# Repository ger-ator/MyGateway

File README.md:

# MyGateway
RFM69 + ATSHA204A Shield for Arduino.

# Description
This is another shield to build a MySensors gateway with Arduino UNO form factor. 
It includes RFM69 radio module and ATSHA204A crypto signing chip.

# Configuration
There are two jumpers to configure CS and IRQ RFM69 pins.
JP1 is used to choose between pins 6 or 10 for the RFM69 CS line. This is necessary to use an ethernet module in the same SPI bus.
JP2 is used to choose between pins 2 or 3 for the RFM69 IRQ line. Default for ATmega328P seems to be pin 2 but for ATmega32u4 is pin 3.
 - Serial gateway using an Arduino UNO JP1 and JP2 should be both 2-3.
 - Ethernet gateway using Arduino UNO with Ethernet shield stacked JP1 should be 1-2 and JP2 2-3.
 - Ethernet gateway with DFRobot DFR0342 JP1 and JP2 should be both 1-2.

# Compact POE powered MySensors ethernet gateway
I have been using the shield with DFRobot DFR0342 board with success. This is a very compact POE powered ethernet gateway setup. DFRobot DFR0342 board is basically an Arduino Leonardo board with built in W5500 ethernet module and POE powered.

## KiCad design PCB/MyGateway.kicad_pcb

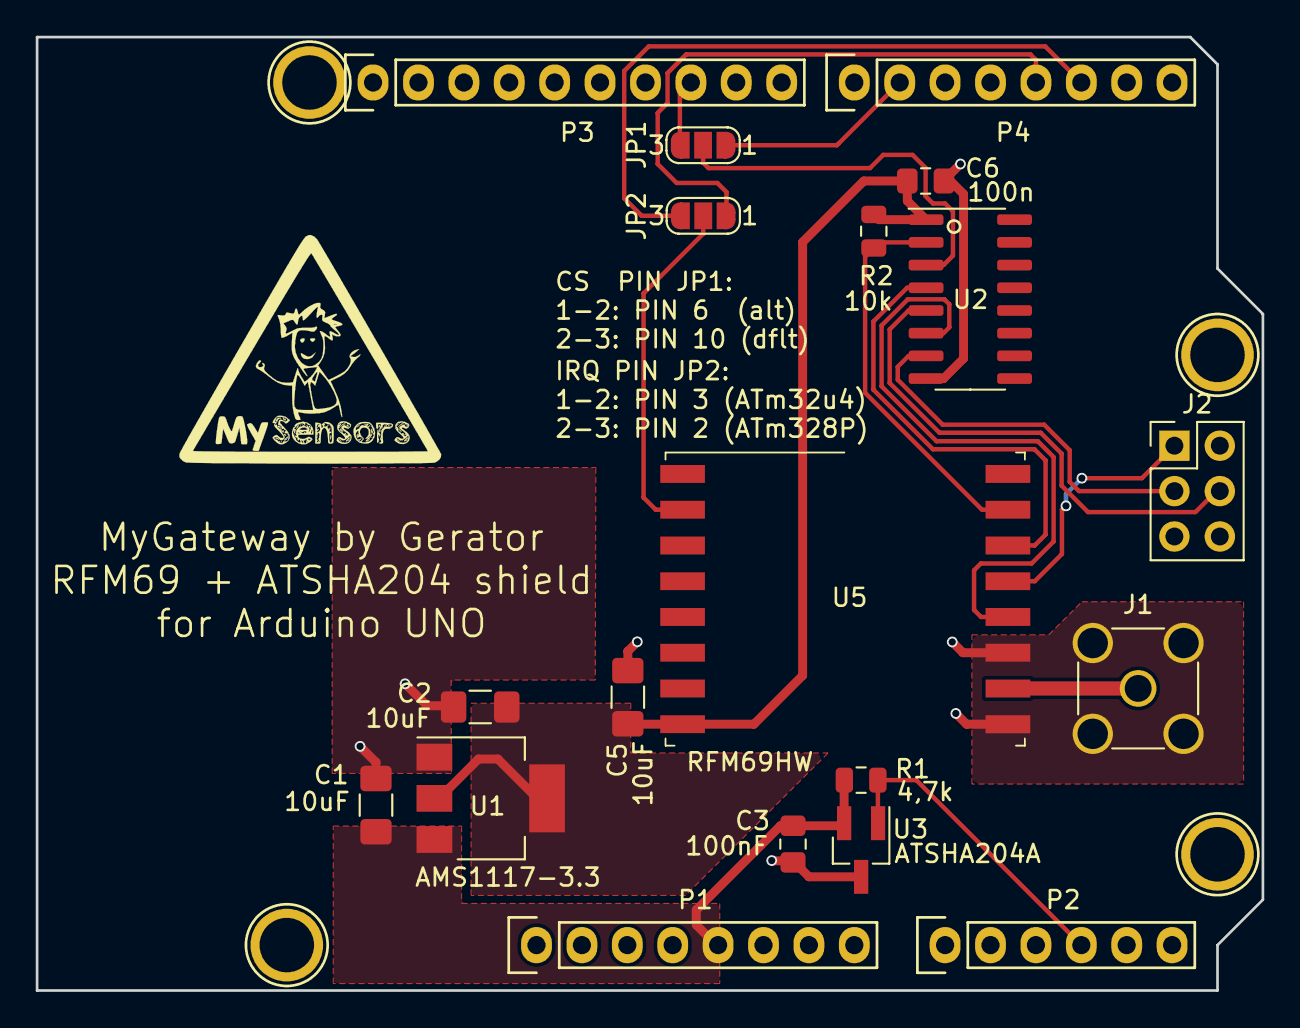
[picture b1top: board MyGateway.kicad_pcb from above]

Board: 2 copper layers, 68.6 x 53.3 mm, 23 parts (0 on the bottom side), 19 nets.

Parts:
C1, C2, C5: 10uF; C_1206_3216Metric_Pad1.42x1.75mm_HandSolder
C3: 100nF; C_0805_2012Metric_Pad1.15x1.40mm_HandSolder
C6: 100n; C_0805_2012Metric_Pad1.15x1.40mm_HandSolder
J1: Conn_Coaxial; SMA_Amphenol_901-144_Vertical
J2: Conn_02x03_Odd_Even; PinHeader_2x03_P2.54mm_Vertical
JP1, JP2: SolderJumper_3_Open; SolderJumper-3_P1.3mm_Open_RoundedPad1.0x1.5mm_NumberLabels
P1: Power; Socket_Strip_Arduino_1x08
P2: Analog; Socket_Strip_Arduino_1x06
P3: Digital; Socket_Strip_Arduino_1x10
P4: Digital; Socket_Strip_Arduino_1x08
P5, P6, P7, P8: CONN_01X01; Arduino_1pin
R1: 4,7k; R_0805_2012Metric
R2: 10k; R_0805_2012Metric
U1: AMS1117-3.3; SOT-223-3_TabPin2
U2: 4050; SOIC-16_3.9x9.9mm_P1.27mm
U3: ATSHA204A; SOT-23_Handsoldering
U5: RFM69HW; HOPERF_RFM69HW

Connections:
+5V: C1.1, C3.1, P1.5, R1.1, U1.3, U3.2
/2: JP2.3, P4.6
/3(**): JP2.1, P4.5
/6(**): JP1.1, P4.2
/10(**/SS): JP1.3, P3.8
/A3: P2.4, R1.2, U3.1
/A4(SDA): P2.5, P3.2
/A5(SCL): P2.6, P3.1
/CSN: R2.2, U2.2, U5.15
/IRQ: JP2.2, U5.2
/MISO: J2.1, U5.13
/MOSI: U2.4, U5.14
/MOSI-ICSP: J2.4, U2.5
/SCK: U2.6, U5.12
/SCK-ICSP: J2.3, U2.7
GND: C1.2, C2.2, C3.2, C5.2, C6.2, J1.2, P1.6, P1.7, P3.4, U1.1, U2.8, U3.3, U5.9, U5.11
unnamed: J1.1, U5.10
unnamed: JP1.2, U2.3
VCC: C2.1, C5.1, C6.1, R2.1, U1.2, U2.1, U5.8

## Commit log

2020-08-16 Update README.md
    Initial commit
2020-08-16 Initial commit.
2020-08-17 Update README.md
    Mistype.
2020-08-18 Added picture of DFRobot Ethernet gateway.
2020-08-24 Disable USB code to save flash and enable Inclusion.
2020-08-24 Added some pics
